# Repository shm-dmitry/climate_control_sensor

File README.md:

Project info
=======

*DEPRECATED. New board/fw project in https://github.com/shm-dmitry/air-detector*

This module allows you to control climate in room.

It reports:
- CO2 value
- Temperature
- Humidity
- Pressure
- PMx value
- Illumination
- Direction and speed of air in ventilation  

It controls:
- Exhaust fan 
- Cooling fan with speed control (fan_pwm driver) 
- Control any device (except Air Conditioneers at now) via IR
- TION Breather (in development at now...) via Bluetooth

Additional features:
- Integrates with any smart-house system via MQTT protocol (over WIFI)
- Contains touchpad supports multi-click (single click, double click, tripple click etc)
- Contains RGB led to indicate some internal state you want

Project status
=======

Schematics is done.
Board is done.

| Sensor | Software | Hardware |
| --- | --- | --- |
| TION 3S | In progress | - |
| BME280 | OK | OK |
| SGP30 | OK | OK |
| BH1750 | OK | OK |
| MH-Z19B | OK | OK |
| PMS7003 | OK | OK |
| Internal ESP32 Touch Pin | OK | OK |
| RGB Led | OK | OK |
| FAN Switch control | OK | OK |
| FAN speed control | OK | OK |
| IR Transmitter | OK | OK |
| Anemometer | OK | OK |

Install guide
===========

Hardware:

1. Install EAGLE. Freeware version is OK: https://www.autodesk.com/products/eagle/free-download
2. Open board (lw_board.brd)
3. Generate CAM data and make order on any factory

Software
1. Install ESP-IDF SDK https://docs.espressif.com/projects/esp-idf/en/latest/esp32/get-started/index.html
2. Clone and open project. 
3. Open `sdkconfig` and setup project settings. You can enable or disable unused options in `Climate Control Configuration` menu.
4. Build and flash ESP32 Devkit

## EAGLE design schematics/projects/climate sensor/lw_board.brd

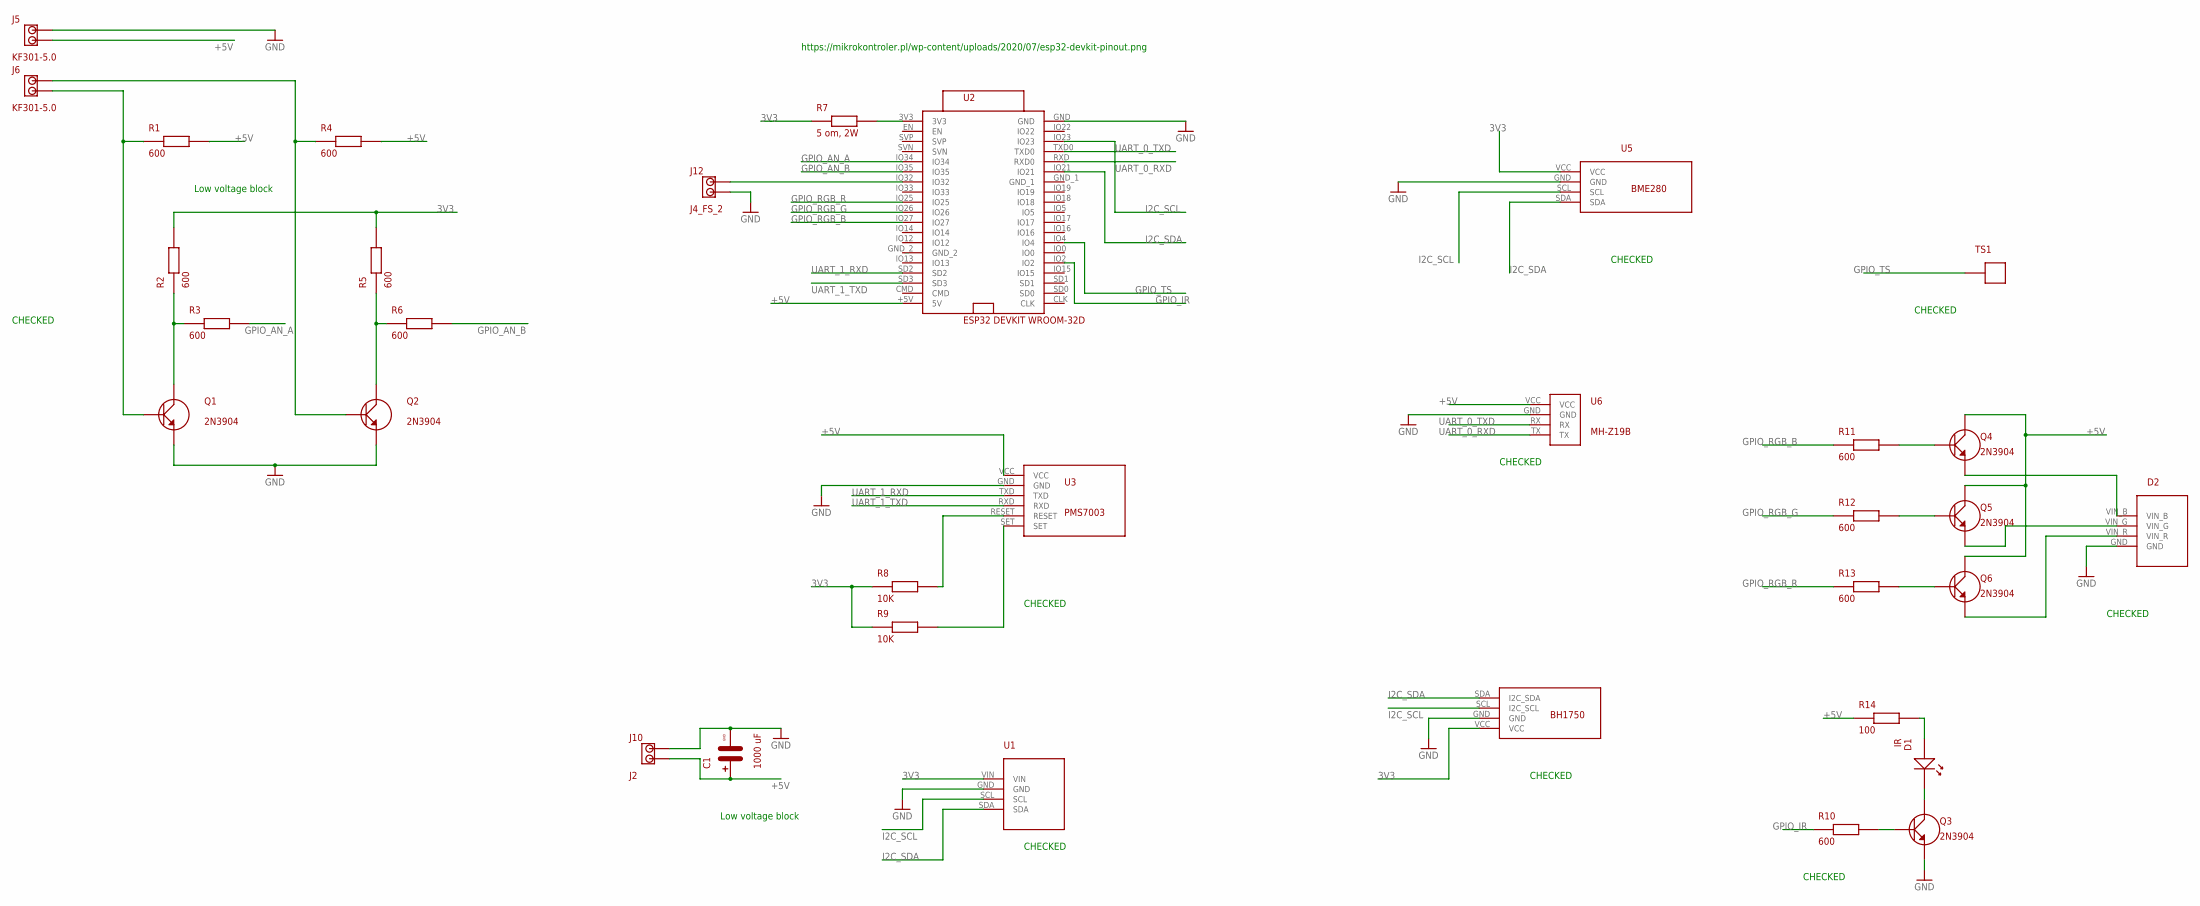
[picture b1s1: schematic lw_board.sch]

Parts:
C1: 1000 uF; C
D1: IR; LD
D2: RGBLED
J5, J6: KF301-5.0; J2
J10: J2
J12: J4_FS_2; J2
Q1, Q2, Q3, Q4, Q5, Q6: 2N3904; TRANSISTOR
R1, R2, R3, R4, R5, R6, R10, R11, R12, R13: 600; R
R7: 5 om, 2W; R
R8, R9: 10K; R
R14: 100; R
TS1: TOUCH_SENSOR
U1: GY-SGP30
U2: ESP32 DEVKIT WROOM-32D; ESP32
U3: PMS7003; PMS7003_J
U4: BH1750
U5: BME280
U6: MH_Z19B

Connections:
3V3: R2.P$2, R5.P$2, R7.P$1, R8.P$1, R9.P$1, U1.VIN, U4.VCC, U5.VCC
+5V: C1.PIN_PLUS, J5.PIN_2, J10.PIN_2, Q4.C, Q5.C, Q6.C, R1.P$2, R4.P$2, R14.P$1, U2.+5V (5V), U3.VCC, U6.VCC
GND: C1.PIN_GND, D2.GND, J5.PIN_1, J10.PIN_1, J12.PIN_2, Q1.E, Q2.E, Q3.E, U1.GND, U2.GND, U3.GND, U4.GND, U5.GND, U6.GND
GPIO_AN_A: R3.P$2, U2.IO34
GPIO_AN_B: R6.P$2, U2.IO35
GPIO_IR: R10.P$1, U2.IO2
GPIO_RGB_B: R11.P$1, U2.IO27
GPIO_RGB_G: R12.P$1, U2.IO26
GPIO_RGB_R: R13.P$1, U2.IO25
GPIO_TS: TS1.P$1, U2.IO4
I2C_SCL: U1.SCL, U2.IO23, U4.SCL (I2C_SCL), U5.SCL
I2C_SDA: U1.SDA, U2.IO21, U4.SDA (I2C_SDA), U5.SDA
unnamed: D2.VIN_B, Q4.E
unnamed: D2.VIN_G, Q5.E
unnamed: D2.VIN_R, Q6.E
unnamed: J6.PIN_1, Q2.B, R4.P$1
unnamed: J6.PIN_2, Q1.B, R1.P$1
unnamed: Q1.C, R2.P$1, R3.P$1
unnamed: Q2.C, R5.P$1, R6.P$1
unnamed: R8.P$2, U3.RESET
unnamed: J12.PIN_1, U2.IO32
unnamed: Q4.B, R11.P$2
unnamed: Q5.B, R12.P$2
unnamed: Q6.B, R13.P$2
unnamed: R7.P$2, U2.3V3
unnamed: D1.PIN_ANODE, Q3.C
unnamed: D1.PIN_CATHODE, R14.P$2
unnamed: Q3.B, R10.P$2
unnamed: R9.P$2, U3.SET
UART_0_RXD: U2.RXD (RXD0), U6.TX
UART_0_TXD: U2.TXD0, U6.RX
UART_1_RXD: U2.SD2, U3.TXD
UART_1_TXD: U2.SD3, U3.RXD

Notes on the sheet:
https://mikrokontroler.pl/wp-content/uploads/2020/07/esp32-devkit-pinout.png
CHECKED
Low voltage block

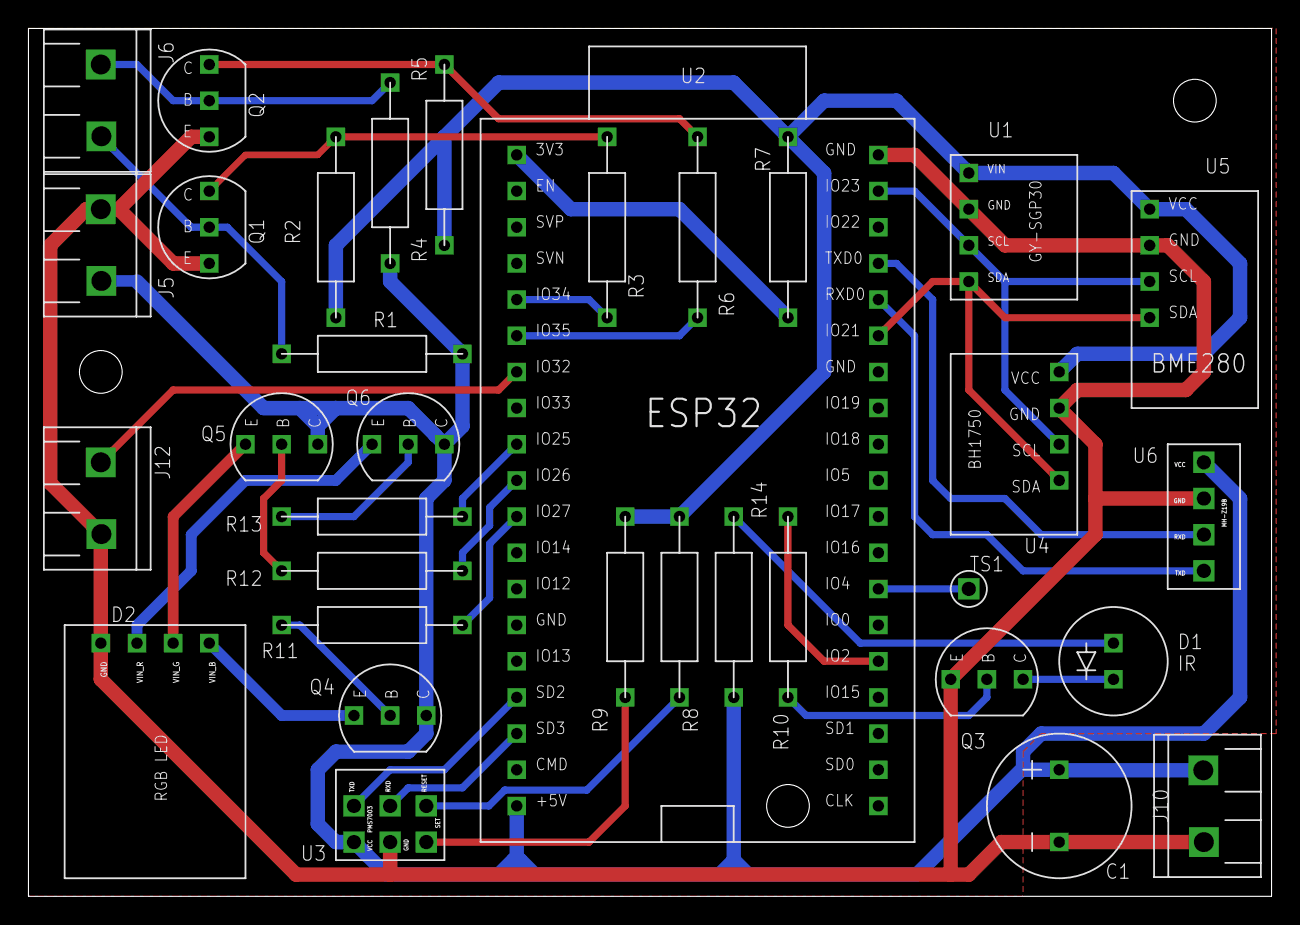
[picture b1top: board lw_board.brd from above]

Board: 2 copper layers, 87.3 x 61.0 mm, 34 parts (0 on the bottom side), 33 nets.

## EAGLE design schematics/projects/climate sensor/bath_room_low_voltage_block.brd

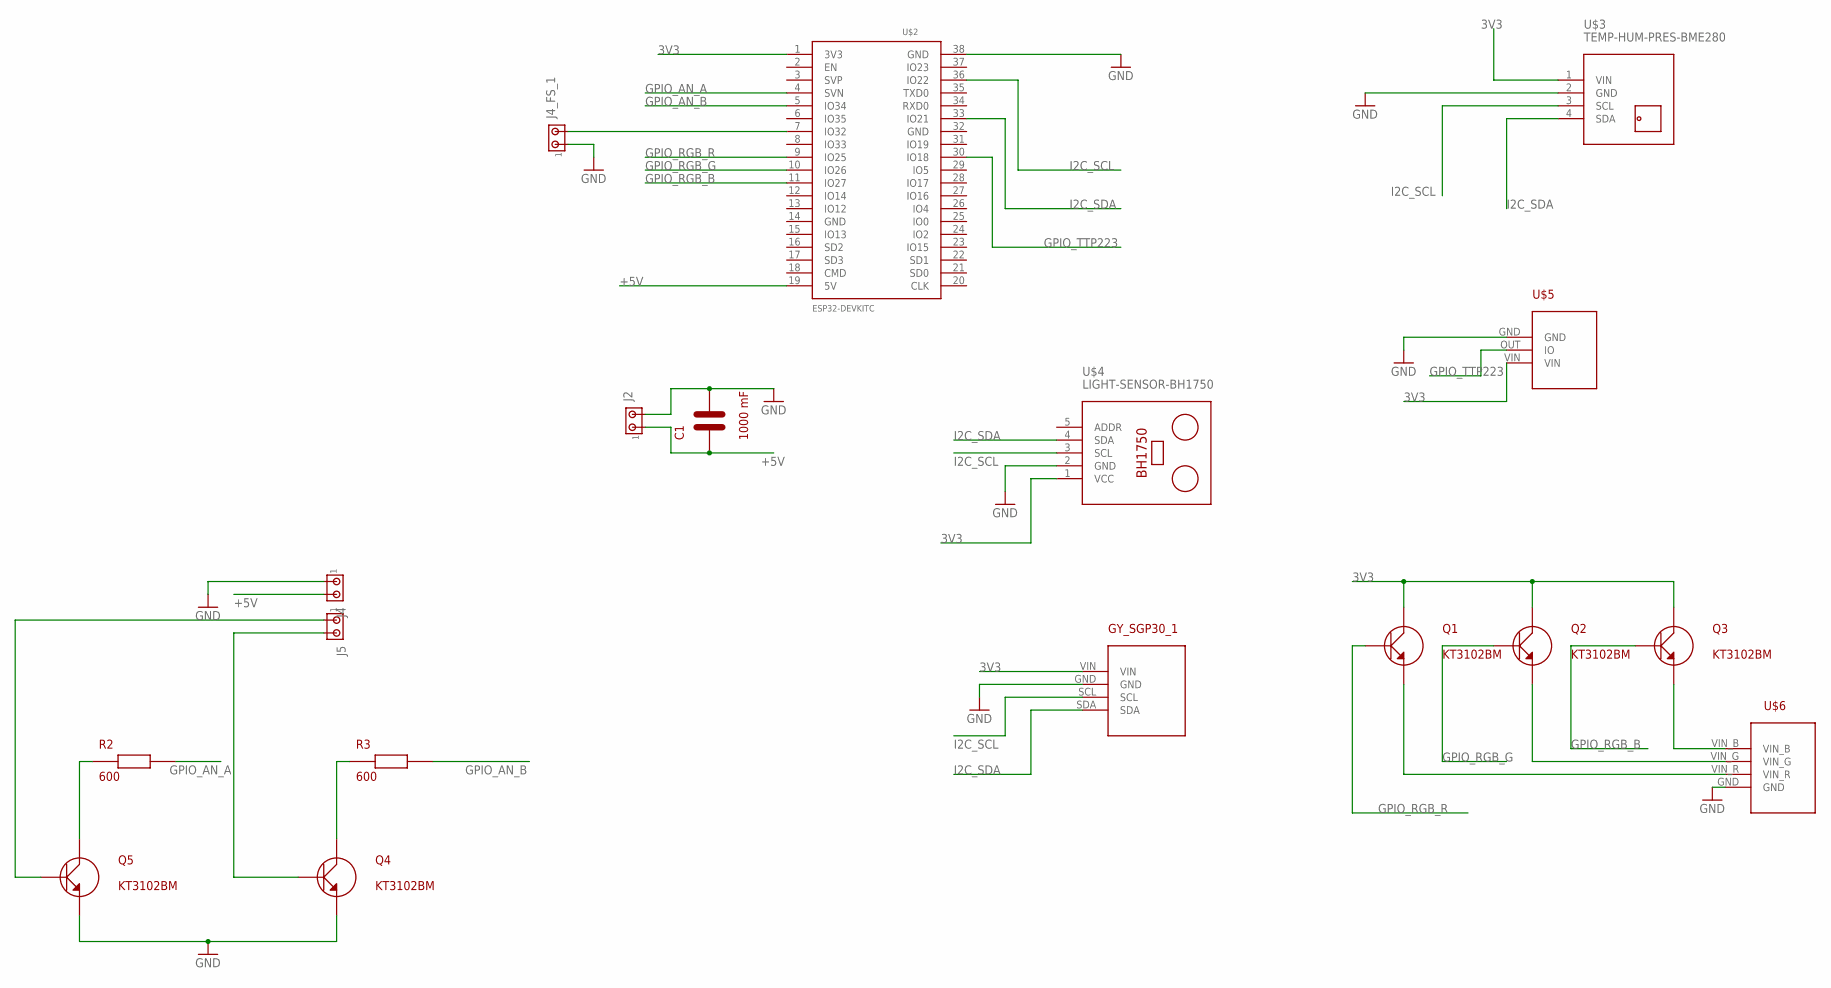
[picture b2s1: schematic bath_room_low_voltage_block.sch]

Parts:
C1: 1000 mF; C
GY_SGP30_1: GY-SGP30
J2, J4, J4_FS_1, J5: MTA02-100; 10X02MTA
Q1, Q2, Q3, Q4, Q5: KT3102BM; TRANSISTOR_NPN
R2, R3: 600; R
U$2: ESP32DEVKITC; ESP32-DEVKITC
U$3: TEMP-HUM-PRES-BME280
U$4: LIGHT-SENSOR-BH1750
U$5: TTP223
U$6: RGBLED

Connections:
3V3: GY_SGP30_1.VIN, Q1.C, Q2.C, Q3.C, U$2.1 (3V3), U$3.1 (VIN), U$4.1 (VCC), U$5.VIN
+5V: C1.P$1, J2.1, J4.2, U$2.19 (5V)
GND: C1.P$2, GY_SGP30_1.GND, J2.2, J4.1, J4_FS_1.1, Q4.E, Q5.E, U$2.38 (GND), U$3.2 (GND), U$4.2 (GND), U$5.GND, U$6.GND
GPIO_AN_A: R2.P$2, U$2.4 (SVN)
GPIO_AN_B: R3.P$2, U$2.5 (IO34)
GPIO_RGB_B: Q3.B, U$2.11 (IO27)
GPIO_RGB_G: Q2.B, U$2.10 (IO26)
GPIO_RGB_R: Q1.B, U$2.9 (IO25)
GPIO_TTP223: U$2.30 (IO18), U$5.OUT (IO)
I2C_SCL: GY_SGP30_1.SCL, U$2.36 (IO22), U$3.3 (SCL), U$4.3 (SCL)
I2C_SDA: GY_SGP30_1.SDA, U$2.33 (IO21), U$3.4 (SDA), U$4.4 (SDA)
unnamed: J4_FS_1.2, U$2.7 (IO32)
unnamed: Q3.E, U$6.VIN_B
unnamed: Q2.E, U$6.VIN_G
unnamed: Q1.E, U$6.VIN_R
unnamed: J5.1, Q5.B
unnamed: J5.2, Q4.B
unnamed: Q5.C, R2.P$1
unnamed: Q4.C, R3.P$1

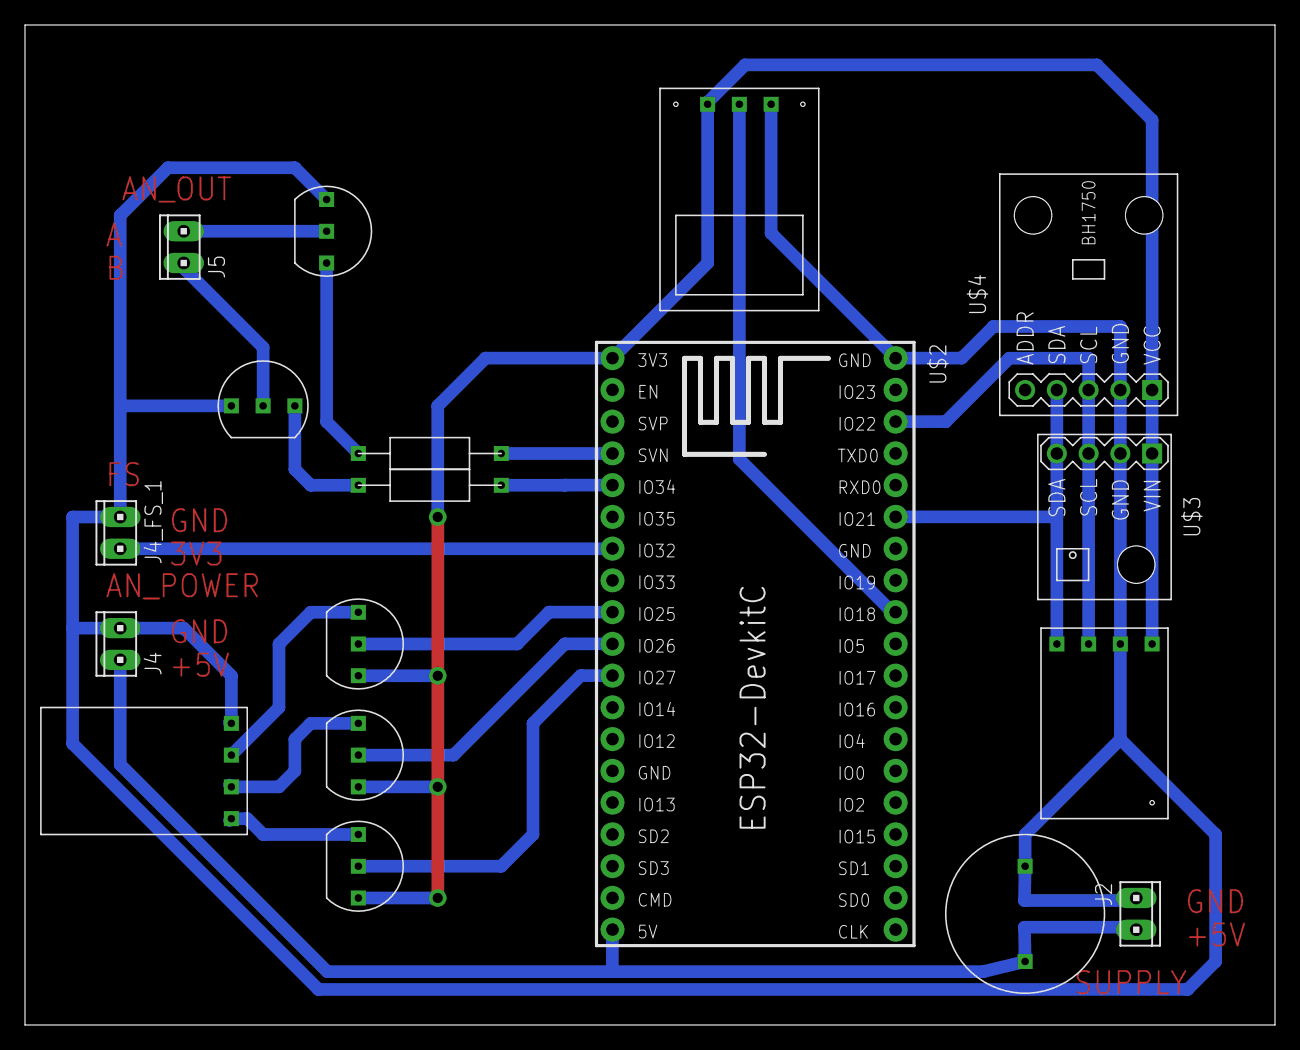
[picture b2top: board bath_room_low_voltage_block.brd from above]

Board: 2 copper layers, 100.0 x 80.0 mm, 18 parts (0 on the bottom side), 19 nets.

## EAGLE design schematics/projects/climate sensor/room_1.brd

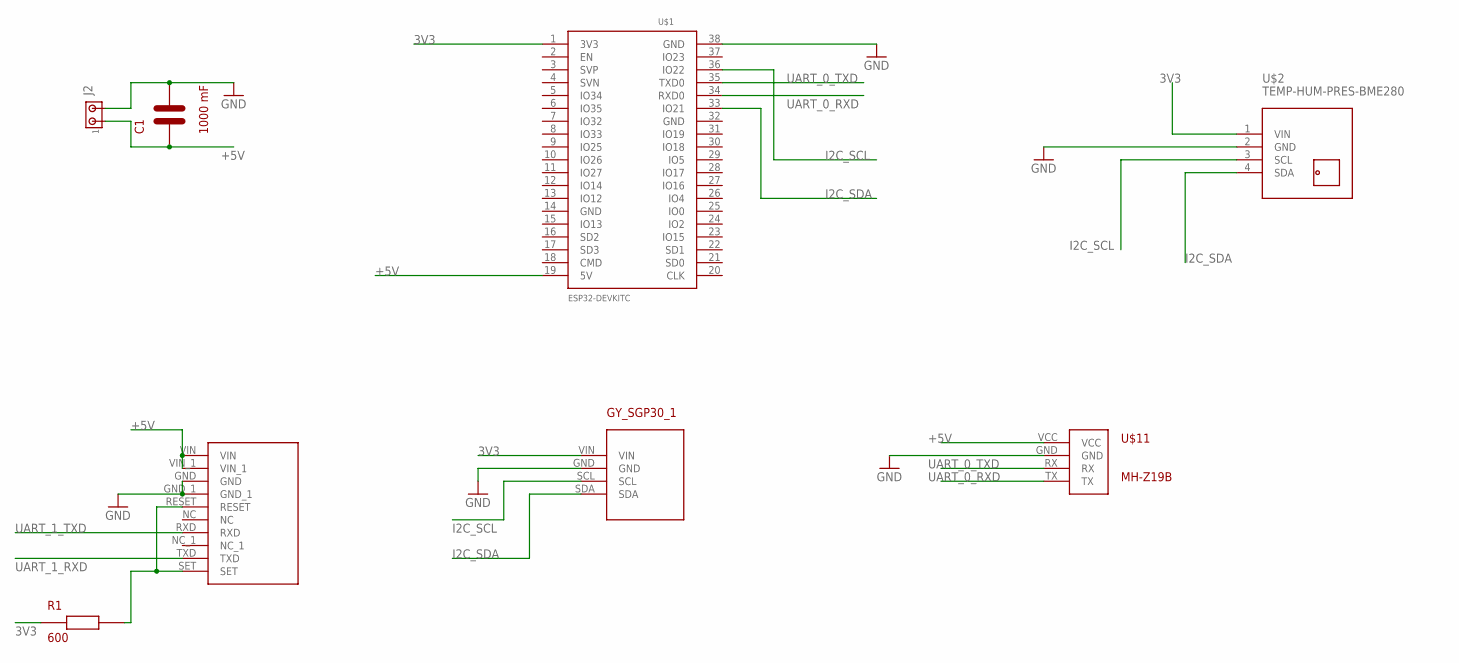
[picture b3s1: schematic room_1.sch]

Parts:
C1: 1000 mF; C
GY_SGP30_1: GY-SGP30
J2: MTA02-100; 10X02MTA
R1: 600; R
U$1: ESP32DEVKITC; ESP32-DEVKITC
U$2: TEMP-HUM-PRES-BME280
U$3: PMS7003
U$11: MH_Z19B

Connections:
3V3: GY_SGP30_1.VIN, R1.P$1, U$1.1 (3V3), U$2.1 (VIN)
+5V: C1.P$1, J2.1, U$1.19 (5V), U$3.VIN, U$3.VIN_1, U$11.VCC
GND: C1.P$2, GY_SGP30_1.GND, J2.2, U$1.38 (GND), U$2.2 (GND), U$3.GND, U$3.GND_1, U$11.GND
I2C_SCL: GY_SGP30_1.SCL, U$1.36 (IO22), U$2.3 (SCL)
I2C_SDA: GY_SGP30_1.SDA, U$1.33 (IO21), U$2.4 (SDA)
unnamed: R1.P$2, U$3.RESET, U$3.SET
UART_0_RXD: U$1.34 (RXD0), U$11.TX
UART_0_TXD: U$1.35 (TXD0), U$11.RX
UART_1_RXD: U$3.TXD
UART_1_TXD: U$3.RXD

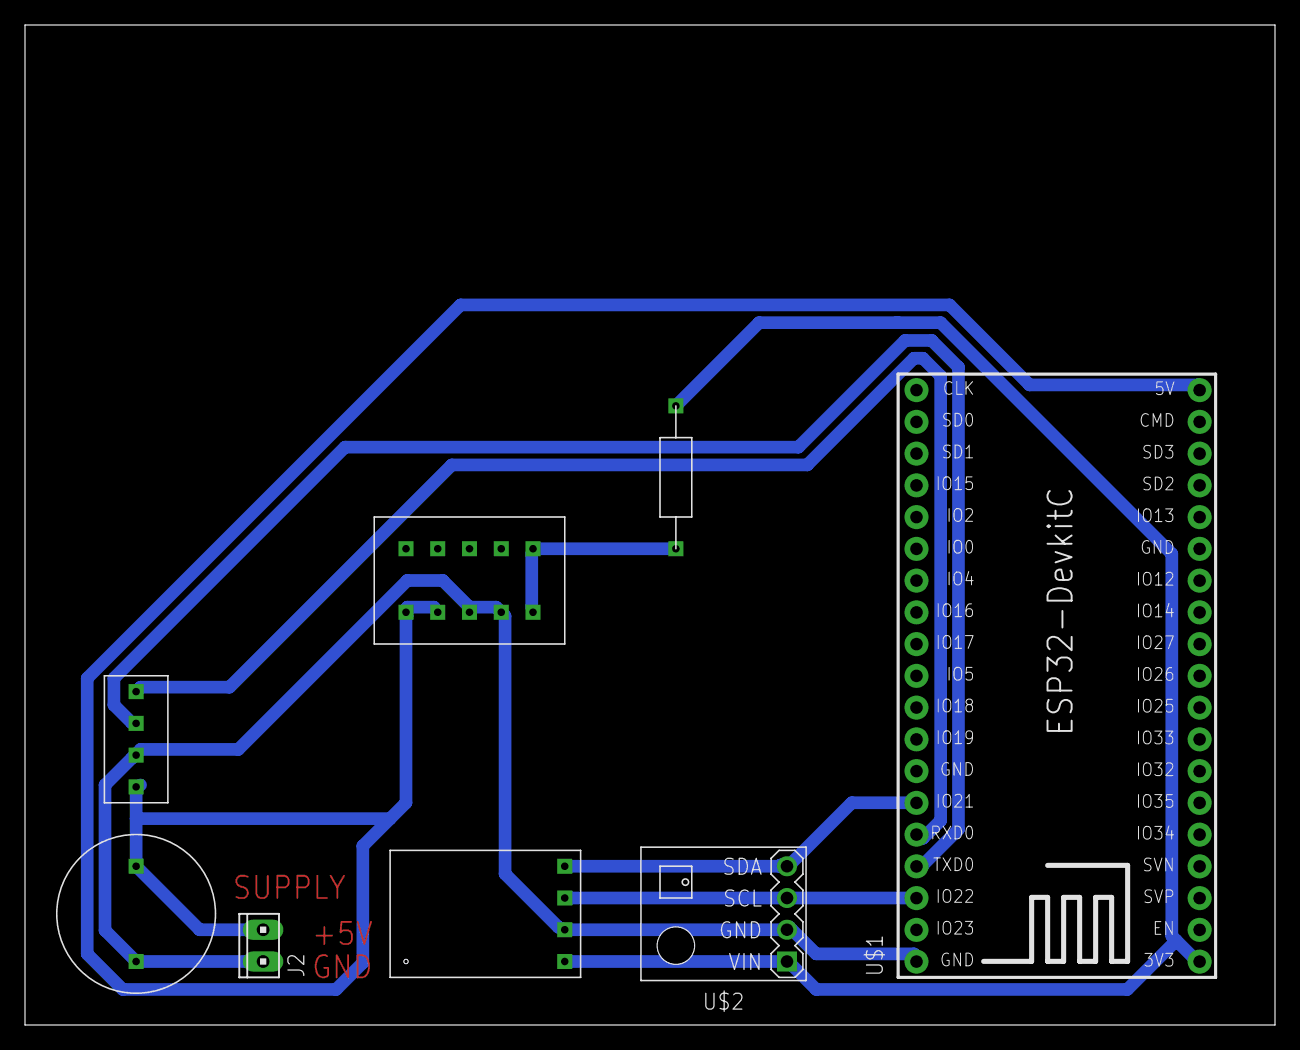
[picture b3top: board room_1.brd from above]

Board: 2 copper layers, 100.0 x 80.0 mm, 8 parts (0 on the bottom side), 8 nets.

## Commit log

2021-02-11 Initial commit. Not tested yet!
2021-02-18 fix resolution - 16 bit per color
2021-02-18 EAGLE schematics for this project with local component library
2021-02-18 pin numbers synchronized with schematics
2021-02-18 added eagle board files for low-voltage schemas
2021-02-18 changes in board files.
2021-03-24 actualized schematics
2021-03-24 added IR interface
2021-03-24 added buildin touch sensor, maybe I will use it.
2021-03-24 remove unused files
2021-03-29 Custom partiton mapping
2021-03-29 usused file
2021-03-29 added sdkconfig to gitignore
2021-03-30 CO2 sensor works now.
2021-03-30 PMS7003 works now
2021-03-30 Corrected schematics for PMS7003
2021-03-30 touchpad integration (not tested yet)
2021-03-30 touchpad works, but I have to work with hardware to detect action on some distance from sensor
2021-03-31 Changed touchpad logic: 1. support autocalibration 2. support double-tripple-multi clicks 3. removed ISR
2021-03-31 Removed TTP223 integration. Removed TTP223 from schematics Added logs to FAN integration (prepare for upcoming debug)
2021-03-31 Update sdkconfig
    Removed TTP223 lines from unstaged file
2021-04-01 touchpad driver: added on_cliock event fan_switch: tested and worked.
2021-04-01 Start working on anemometer driver
2021-04-01 anemometer - driver works
2021-04-01 anemometer hardware works
2021-04-01 Added and tested IR transmitter functionality
2021-04-01 fix strcmp call
2021-04-02 Prepare library and schematics to create board
2021-04-02 Continue prepare schematics to create board
2021-04-02 rgbled checked and works
2021-04-02 Added low-voltage-block schema First version of low-voltage-block board
2021-04-03 continue work with board
2021-04-03 rename elements, optimize board
2021-04-03 Board is DONE
2021-04-06 add RGB LED calibration
2021-04-06 change argument in ledc_fade_func_install (it was mistake)
2021-04-11 Work under I2C bus. BME280 - tested BH1750 - tested
2021-04-11 SGP30 sensor works now. I2C bus fully tested.
2021-04-11 rename threads
2021-04-19 1. mqtt - fix memory allocation in subscribe method. 2. logs - rename LOG define 3. tion - working under TION integration module
2021-04-20 Working under TION driver. BT restarts successfully on error. Timeout checker works fine. Some code refactoring.
2021-04-22 Fixed issues in board.
    I received board from jlcpcb
    This commit fixed issues in board:
    1. drill size increased - it was too small for some components.
    2. 'J2' component in library was re-drawed using sizes from datasheet
    3. Textes for J2 component was increased in size and moved to bPlace
    layer (bottom layer). On top layer not enougth space for it.
2021-04-23 fix copy-paste error in IR Transmitter module
2021-04-26 wifi: ability to change AP sensor connected to.
    WIFI Connector listens for a message in MQTT topic with new
    SSID/PASSWORD.
    After receiving message it saves credentials in NVS and restarts.
    On 'boot' process sensor tryed to connect to WiFi AP
    1. using saved credentials if exists
    2. using configured credentials if saved credentials absent or AP
2021-05-06 I assembled device and it worked!
2021-05-09 Added ability to recalibrate SGP30 sensor (on hot-replace for example to another module)
2021-05-28 Commit schematics for a window control project
2021-05-28 Changed some nomanals during making order
2021-07-02 added fan_pwm driver
2021-07-02 Update readme - added information about fan_pwm module
2021-07-04 FAN PWM speed control - updated driver and schematics. Driver tested on RQD2510LS fan and its worked on 30...100% speed
2021-07-07 MH-Z19B start producing wrong data... Trying to find reason..
2021-07-08 I have problem with MH-Z19B sensor. I think problem with auto-calibration witch auto-executed after one day warks. So 1. Added real-time logging to MQTT 2. During startup added READ operation witch c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
2021-07-19 move window-control schema to separete project
2021-07-19 fix some logging mistakes
2021-07-21 touchpad threshold modified to work on 2sm ditance
2021-08-20 1. changed FAN_PWM driver 2. added default values to Kconfig.projbuild
2021-10-29 fixes in touchpad sensor
2021-10-30 Added 3D models for anemometer
2022-01-26 Added 3D model box for CO2 / Humidity / Temperature / TVOC sensors configuration
2022-01-26 actualized library used in other projects
2022-02-22 Changed box 3D model

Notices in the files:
parts and their libraries:
diy-modules: Released under the Creative Commons Attribution 4.0 International License: http://creativecommons.org/licenses/by/4.0
